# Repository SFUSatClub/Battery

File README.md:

# Battery Board
KiCad project for the cubesat battery board. This board holds 2 18650 cells in series with protection circuitry. This board follows PC104 dimentions.

This repository uses the SFU Satellite Team's KiCad component library as a submodule.
To start working on the repository:

```
1. Open a git shell
2. Navigate to the directory you wish to place the repository inside
3. git clone --recursive "https://github.com/SFUSatClub/Battery.git"
```

If you modify either the component schematic or footprint libraries you must push those changes to the SFUSatClub/KiCad-Lib repository, then commit the project repository.

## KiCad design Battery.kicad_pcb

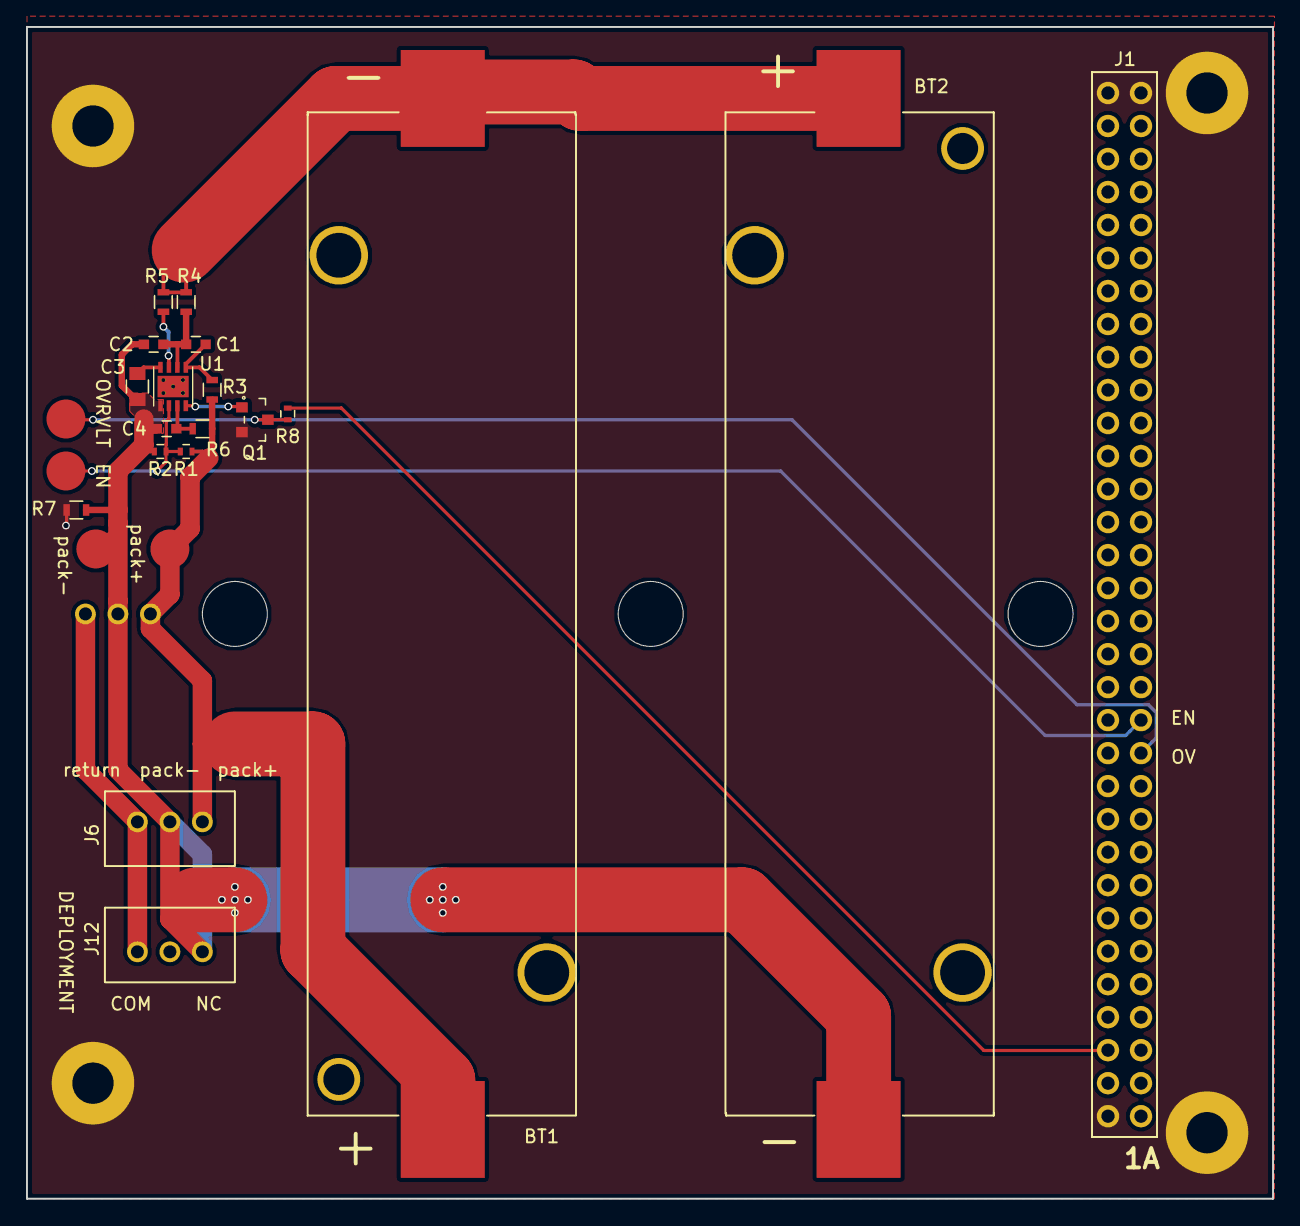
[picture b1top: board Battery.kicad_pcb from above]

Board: 2 copper layers, 95.9 x 90.2 mm, 28 parts (1 on the bottom side), 14 nets.

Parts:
BT1, BT2: Battery_Cell; 1042-BattHolder
C1, C2, C4: 0.1uF; C_0603
C3: 0.33uF; C_0805
J1: PC104-8BIT; PC104-8bit
J2, J3, J4, J5: PC104PTH
J6, J11, J12: B3B-XH-A(LF)(SN); B3B-XH-A
J7, J8, J9, J10: TEST_1P; Measurement_Point_Round-SMD-Pad_Big
Q1: 2N7002ET1G; SOT-23-3
R1: DNP; R_0402
R2: 1k; R_0402
R3: 160R; R_0603
R4: 250R; R_0603
R5, R6: 100R; R_0603
R7: DNP; R_0603
R8: R_10k0_1%_0.063W_0402; R_0402
U1: BQ29209; VDFN-8

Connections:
+3V3: J1.3B, R8.1
/OVR_VLT: J1.12A, J8.1, Q1.3, R8.2
/SeriesBatteryCell/PACK+: BT1.1, J6.1, J9.1, J11.3, R1.1, R3.1, R6.1
/SeriesBatteryCell/PACK-: BT2.2, C2.2, C3.2, C4.2, J6.2, J10.1, J11.2, J12.3, R2.2, R7.1, U1.5
/~CB_EN: J1.13A, J7.1, R1.2, R2.1, U1.6
GND: J1.1B, J1.32A, J1.32B, J2.1, J3.1, J4.1, J5.1, Q1.2, R7.2
unnamed: BT1.2, BT2.1, R4.1, R5.1
unnamed: C1.1, R3.2, U1.1
unnamed: C1.2, C2.1, R4.2, U1.2
unnamed: C3.1, U1.4
unnamed: C4.1, R6.2, U1.7
unnamed: J6.3, J11.1, J12.1
unnamed: R5.2, U1.3
OUT: Q1.1, U1.8

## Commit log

2018-03-05 balancing enabled by default using 1k PD. Can override by pulling line high from OBC
2018-03-15 layout complete
2018-03-22 moved bottom side DC connector to avoid the RFB pin path on the eps board
2018-03-22 generated gerbers
2018-03-22 added production doc
2018-04-28 Revision 2. Fixed silkscreen labelling issue with EN/OVR_VLT test points, Added level shifter for OVR_VLT output as IC outputs more than 3.3V
2018-04-29 added soldermask width requirement to fab notes
